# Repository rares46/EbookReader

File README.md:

# EbookReader
OpenBook eBook Reader

Dispozitivul e-book se bazeaza pe un microcontroller ESP32-C6 si include un afisaj E-Paper.

[Diagrama Bloc](Images/diagram.png)

`Diagrama bloc afiseaza componente:`
- ESP32-C6 (unitate centrala)
- Afisaj E-Paper
- Cititor SD card
- RTC DS3231
- Senzor ambiental BME688
- Control incarcare baterie Li-Po
- Modul flash extern 64MB
- Interfata USB-C
- Circuit de reglare tensiune (LDO)

### BOM - Bill Of Materials

[Fisier BOM](Manufacturing/BOM.csv)
https://ro.mouser.com/
https://www.comet.srl.ro/

Alimentare
- Alimentare principala prin USB-C.
- Reglator de tensiune LDO (IC4 - XC6204A33) pentru conversia de la 5V la 3.3V.
  
Microcontroller
- ESP32-C6 = unitatea principala ce controleaza restul pieselor.
- Se ocupa cu gestionarea interfetei cu utilizatorul, afisajul EPD, comunicatia cu SD card-ul, RTC si senzorul ambiental.
  
Stocare
- Slot microSD pentru stocare.
- Memorie flash externa W25Q512JVSIQ conectata prin SPI pentru firmware suplimentar sau caching.

### Alocarea pinilor ESP32-C6

| Functie                | Pin ESP32-C6         | Observatii |
|------------------------|----------------------|-------------|
| SD Card                | IO2, IO3, IO4, IO5   | SPI |
| E-Paper Display        | IO8, IO9, IO10       | SPI |
| Senzor BME688          | IO6 (SCL), IO7 (SDA) | I2C |
| RTC DS3231             | IO6 (SCL), IO7 (SDA) | I2C shared |
| Flash extern SPI       | IO0, IO1, IO2        | SPI |
| Boot Button            | IO9                  | Reset GPIO |
| Buton IO               | IO10                 | Control interfata |
| UART Debug             | IO20 (TX), IO21 (RX) | Conexiune seriala |
| Ecran Type Select      | IO18, IO19           | Selectare tip e-paper |

Bugs: La piesa SAMACSYS_PARTS_USB4110GFA erori cu Board OUtline Clearance, care sunt datorate piesei cel mai probabil si din cand in cand eorare de Overlap la fir. Daca scot firul si il pun la loc dispare.
La piesa IND_4828-WE-TPC_WRE 2 erori Copper Width, care probabil sunt de la piesa.
  
La directorul images din proiect sunt imagini cu schematic ul, pcb si 3d si diagrama.

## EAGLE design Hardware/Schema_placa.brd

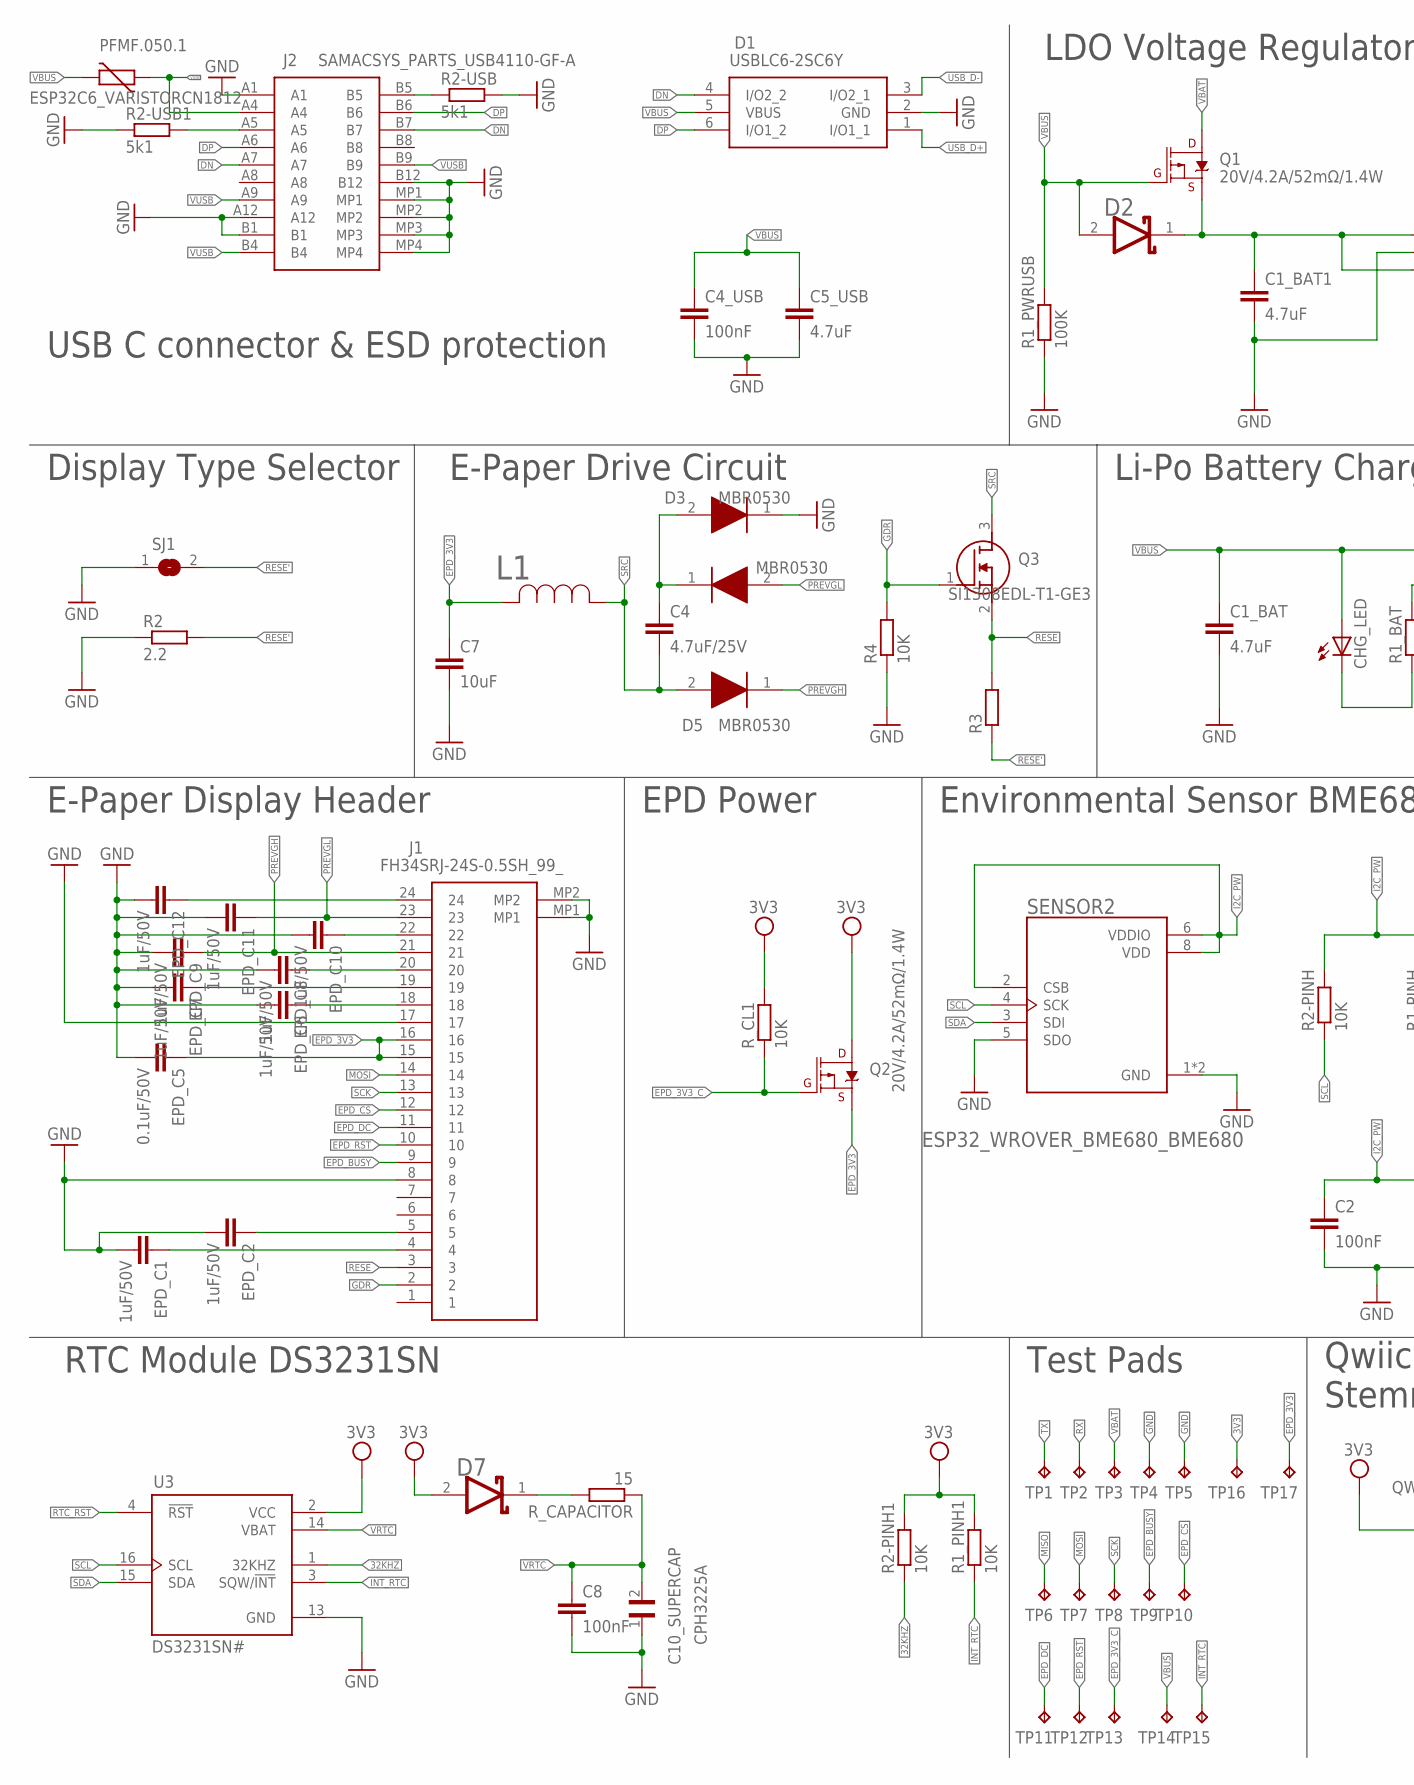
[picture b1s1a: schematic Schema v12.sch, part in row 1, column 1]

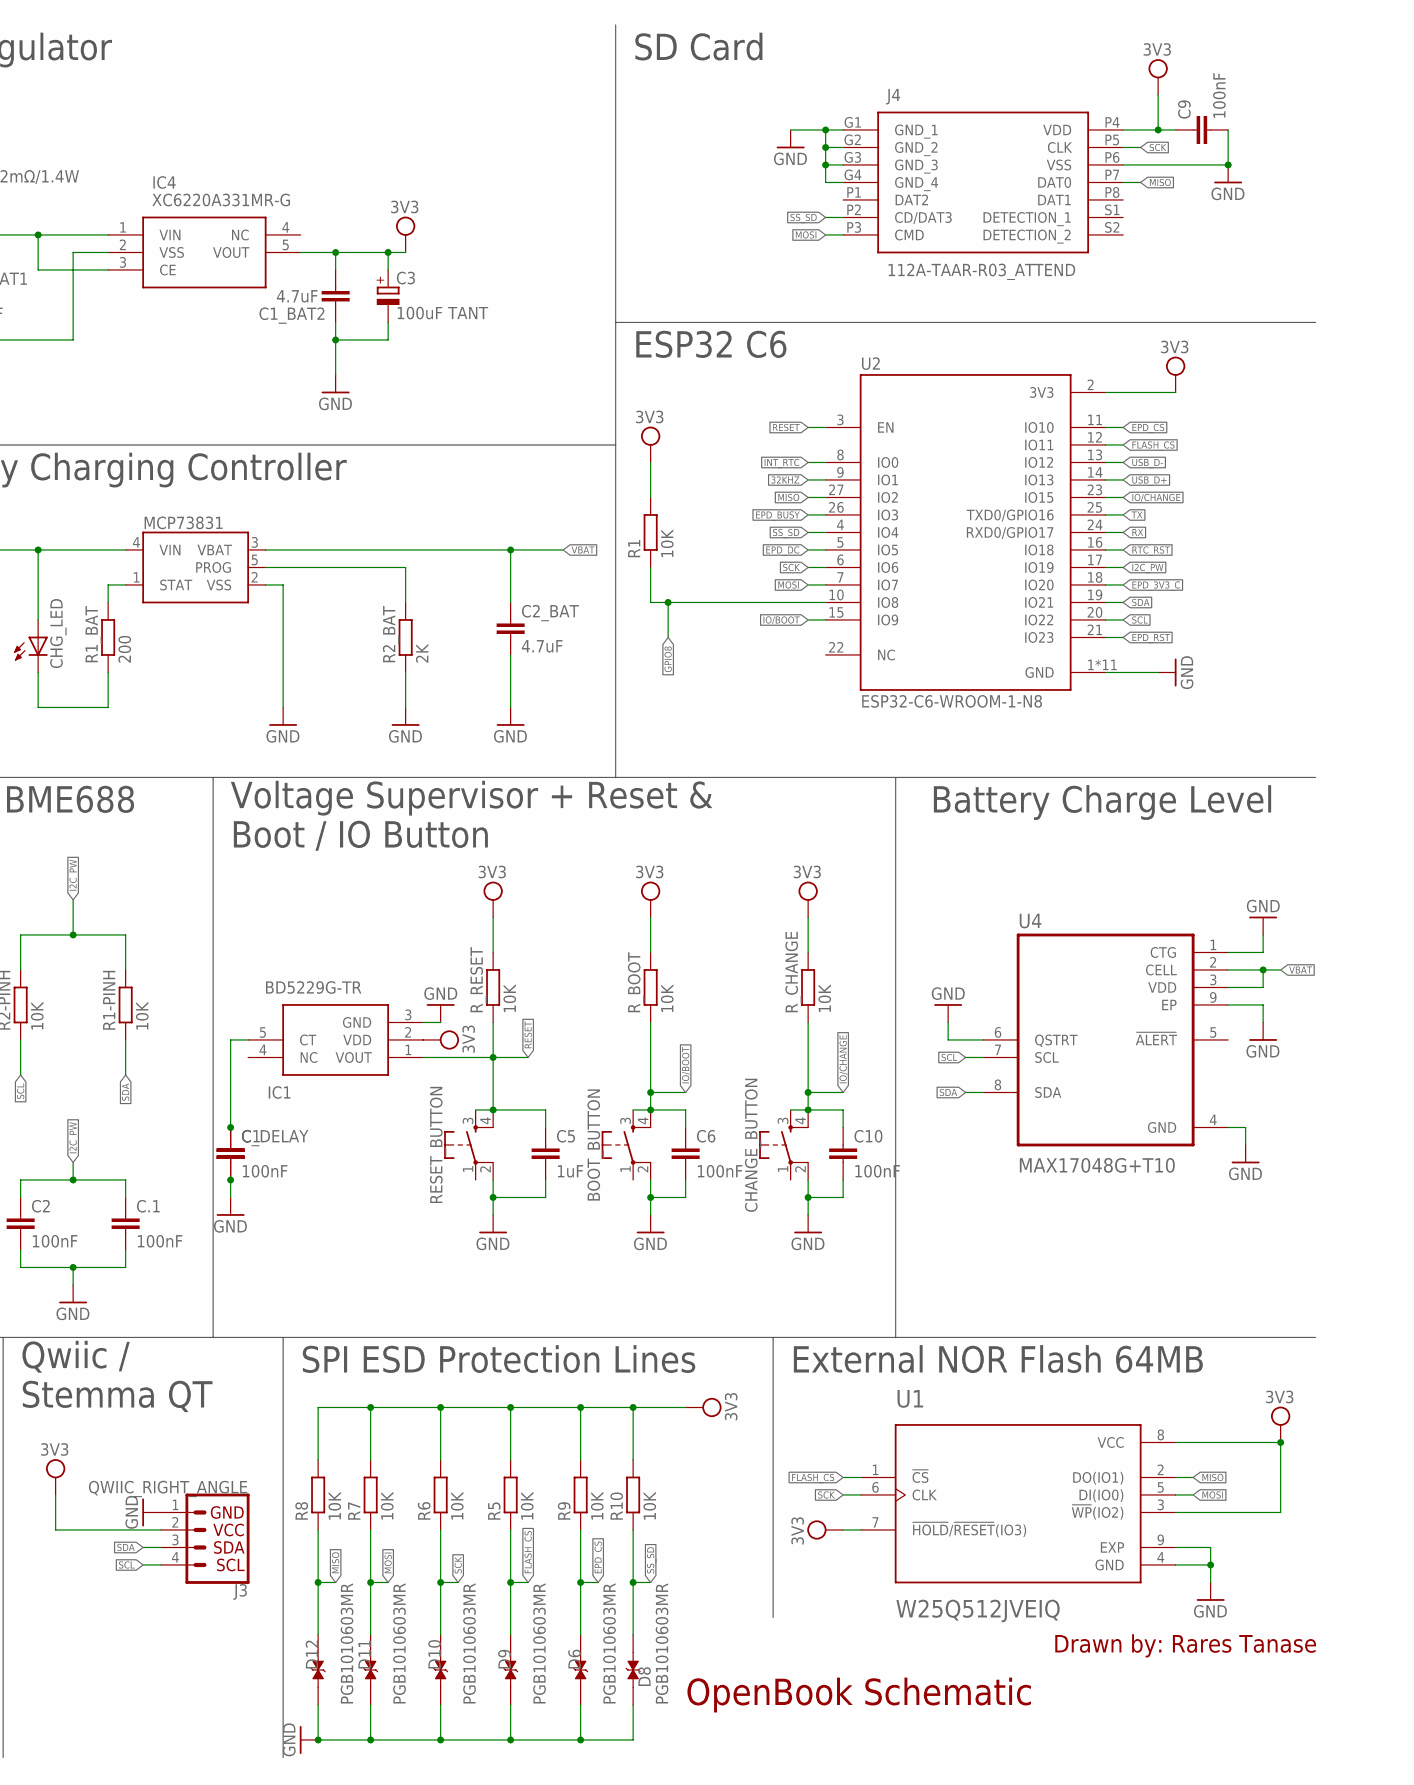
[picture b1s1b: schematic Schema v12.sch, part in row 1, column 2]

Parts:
BOOT_BUTTON: BUTTON_CUSYOMV1; MYBUTTON
C1: ESP32_WROVER_EAGLE-LTSPICE_CC0402; ESP32_WROVER_EAGLE-LTSPICE_C0402
C1_BAT, C1_BAT1, C1_BAT2, C2_BAT, C5_USB: 4.7uF; ESP32_WROVER_EAGLE-LTSPICE_C0402
C2, C4_USB, C6, C8, C9, C10, C.1: 100nF; ESP32_WROVER_EAGLE-LTSPICE_C0402
C3: 100uF TANT; RCL_CT3528
C4: 4.7uF/25V; ESP32_WROVER_EAGLE-LTSPICE_C0402
C5: 1uF; ESP32_WROVER_EAGLE-LTSPICE_C0402
C7: 10uF; ESP32_WROVER_EAGLE-LTSPICE_C0402
C10_SUPERCAP: CPH3225A; CAPCP3225X100N
CHANGE_BUTTON: BUTTON_CUSYOMV1; MYBUTTON
CHG_LED: ADAFRUIT_LEDCHIP-LED0603; ADAFRUIT_CHIP-LED0603
C_DELAY: 100nF; ESP32_WROVER_EAGLE-LTSPICE_C0402
D1: USBLC6-2SC6Y; SOT95P280X145-6N
D2, D7: ESP32_WROVER_AVX---SD0805S020S1R0_AVX_SD0805S020S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; ESP32_WROVER_AVX---SD0805S020S1R0_AVX_SD0805S020S1R0_0
D3, D4, D5: MBR0530; SOD3716X135N
D6, D8, D9, D10, D11, D12: PGB1010603MR; DIOC1608X36N
EPD_C1, EPD_C2, EPD_C6, EPD_C7, EPD_C8, EPD_C9, EPD_C10, EPD_C11, EPD_C12: 1uF/50V; ESP32_WROVER_EAGLE-LTSPICE_C0402
EPD_C5: 0.1uF/50V; ESP32_WROVER_EAGLE-LTSPICE_C0402
IC1: BD5229G-TR; SOT95P280X125-5N
IC4: XC6220A331MR-G; SOT95P280X120-5N
J1: FH34SRJ-24S-0.5SH_99_; FH34SRJ24S05SH99
J2: SAMACSYS_PARTS_USB4110-GF-A; SAMACSYS_PARTS_USB4110GFA
J3: QWIIC_RIGHT_ANGLE; JST04_1MM_RA
J4: 112A-TAAR-R03_ATTEND; 112ATAARR03ATTEND
L1: 744043680IND_4828-WE-TPC_WRE; IND_4828-WE-TPC_WRE
MCP73831: ESP32_WROVER_SPARKFUN-IC-POWER_MCP73831; ESP32_WROVER_SPARKFUN-IC-POWER_SOT23-5
PFMF.050.1: ESP32C6_VARISTORCN1812; ESP32C6_VARISTOR_CT/CN1812
Q1, Q2: 20V/4.2A/52mΩ/1.4W; ESP32_WROVER_SPARKFUN-DISCRETESEMI_SOT23-3
Q3: SI1308EDL-T1-GE3; SOT65P210X110-3N
R1, R1-PINH, R1_PINH1, R2-PINH, R2-PINH1, R4, R5, R6, R7, R8, R9, R10: 10K; ESP32_WROVER_EAGLE-LTSPICE_R0402
R1_BAT: 200; ESP32_WROVER_EAGLE-LTSPICE_R0402
R1_PWRUSB: 100K; ESP32_WROVER_EAGLE-LTSPICE_R0402
R2: 2.2; ESP32_WROVER_EAGLE-LTSPICE_R0402
R2-USB, R2-USB1: 5k1; ESP32_WROVER_EAGLE-LTSPICE_R0402
R2_BAT: 2K; ESP32_WROVER_EAGLE-LTSPICE_R0402
R3: ESP32_WROVER_EAGLE-LTSPICE_RR0402; ESP32_WROVER_EAGLE-LTSPICE_R0402
RESET_BUTTON: BUTTON_CUSYOMV1; MYBUTTON
R_BOOT: 10K; ESP32_WROVER_EAGLE-LTSPICE_R0402
R_CAPACITOR: 15; ESP32_WROVER_EAGLE-LTSPICE_R0402
R_CHANGE: 10K; ESP32_WROVER_EAGLE-LTSPICE_R0402
R_CL1: 10K; ESP32_WROVER_EAGLE-LTSPICE_R0402
R_RESET: 10K; ESP32_WROVER_EAGLE-LTSPICE_R0402
SENSOR2: ESP32_WROVER_BME680_BME680; ESP32_WROVER_BME680_PSON80P300X300X100-8N
SJ1: SJ
TP1, TP2, TP3, TP4, TP5, TP6, TP7, TP8, TP9, TP10, TP11, TP12, TP13, TP14, TP15, TP16, TP17: TPTP20R; TP20R
U1: W25Q512JVEIQ; SON127P600X800X80-9N
U2: ESP32-C6-WROOM-1-N8; XCVR_ESP32-C6-WROOM-1-N8
U3: DS3231SN#; SOIC127P1032X265-16N
U4: MAX17048G+T10; SON50P200X200X80-9N

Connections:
3V3: C1_BAT2.1, C3.+, C9.1, D7.2 (ANODE), IC1.2 (VDD), IC4.5 (VOUT), J3.2, J4.P4 (VDD), Q2.3 (D), R1.2, R1_PINH1.2, R2-PINH1.2, R5.2, R6.2, R7.2, R8.2, R9.2, R10.2, R_BOOT.2, R_CHANGE.2, R_CL1.2, R_RESET.2, TP16.TP, U1.3 (!WP!(IO2)), U1.7 (!HOLD!/!RESET!(IO3)), U1.8 (VCC), U2.2 (3V3), U3.2 (VCC)
32KHZ: R2-PINH1.1, U2.9 (IO1), U3.1 (32KHZ)
DN: D1.4 (I/O2_2), J2.A7, J2.B7
DP: D1.6 (I/O1_2), J2.A6, J2.B6
EPD_3V3: C7.1, EPD_C5.1, J1.15, J1.16, L1.2, Q2.2 (S), TP17.TP
EPD_3V3_C: Q2.1 (G), R_CL1.1, TP13.TP, U2.18 (IO20)
EPD_BUSY: J1.9, TP9.TP, U2.26 (IO3)
EPD_CS: D6.2, J1.12, R9.1, TP10.TP, U2.11 (IO10)
EPD_DC: J1.11, TP11.TP, U2.5 (IO5)
EPD_RST: J1.10, TP12.TP, U2.21 (IO23)
FLASH_CS: D9.2, R5.1, U1.1 (!CS), U2.12 (IO11)
GDR: J1.2, Q3.1 (G), R4.2
GND: BOOT_BUTTON.2, C1.2, C1_BAT.2, C1_BAT1.2, C1_BAT2.2, C2.2, C2_BAT.2, C3.-, C4_USB.2, C5.2, C5_USB.2, C6.2, C7.2, C8.2, C9.2, C10.2, C10_SUPERCAP.1, C.1.2, CHANGE_BUTTON.2, C_DELAY.2, D3.1 (K), D6.1, D8.1, D9.1, D10.1, D11.1, D12.1, EPD_C1.2, EPD_C2.2, EPD_C5.2, EPD_C6.2, EPD_C7.2, EPD_C8.2, EPD_C9.2, EPD_C10.2, EPD_C11.2, EPD_C12.2, IC1.3 (GND), IC4.2 (VSS), J1.8, J1.17, J1.MP1, J1.MP2, J2.A1, J2.A12, J2.B1, J2.B12, J2.MP1, J2.MP2, J2.MP3, J2.MP4, J3.1, J4.G1 (GND_1), J4.G2 (GND_2), J4.G3 (GND_3), J4.G4 (GND_4), J4.P6 (VSS), MCP73831.2 (VSS), R1_PWRUSB.1, R2.1, R2-USB.2, R2-USB1.1, R2_BAT.1, R4.1, RESET_BUTTON.2, SENSOR2.1 (GND), SENSOR2.5 (SDO), SENSOR2.7 (GND), SJ1.1, TP4.TP, TP5.TP, U1.4 (GND), U1.9 (EXP), U2.1 (GND), U2.28 (GND), U2.29_1 (GND), U2.29_2 (GND), U2.29_3 (GND), U2.29_4 (GND), U2.29_5 (GND), U2.29_6 (GND), U2.29_7 (GND), U2.29_8 (GND), U2.29_9 (GND), U3.13 (GND), U4.1 (CTG), U4.4 (GND), U4.6 (QSTRT), U4.9 (EP)
GPIO8: R1.1, U2.10 (IO8)
I2C_PW: C2.1, C.1.1, R1-PINH.2, R2-PINH.2, SENSOR2.2 (CSB), SENSOR2.6 (VDDIO), SENSOR2.8 (VDD), U2.17 (IO19)
INT_RTC: R1_PINH1.1, TP15.TP, U2.8 (IO0), U3.3 (SQW/!INT)
IO/BOOT: BOOT_BUTTON.3, BOOT_BUTTON.4, C6.1, R_BOOT.1, U2.15 (IO9)
IO/CHANGE: C10.1, CHANGE_BUTTON.3, CHANGE_BUTTON.4, R_CHANGE.1, U2.23 (IO15)
MISO: D12.2, J4.P7 (DAT0), R8.1, TP6.TP, U1.2 (DO(IO1)), U2.27 (IO2)
MOSI: D11.2, J1.14, J4.P3 (CMD), R7.1, TP7.TP, U1.5 (DI(IO0)), U2.7 (IO7)
unnamed: C1.1, C_DELAY.1, IC1.5 (CT)
unnamed: J2.B5, R2-USB.1
unnamed: EPD_C2.1, J1.5
unnamed: J2.A5, R2-USB1.2
unnamed: CHG_LED.C, R1_BAT.1
unnamed: C1_BAT1.1, D2.1 (CATHODE), IC4.1 (VIN), IC4.3 (CE), Q1.2 (S)
unnamed: C4.1, D3.2 (A), D4.1 (K)
unnamed: MCP73831.1 (STAT), R1_BAT.2
unnamed: MCP73831.5 (PROG), R2_BAT.2
unnamed: EPD_C1.1, J1.4
unnamed: EPD_C6.1, J1.18
unnamed: EPD_C7.1, J1.19
unnamed: EPD_C8.1, J1.20
unnamed: EPD_C10.1, J1.22
unnamed: EPD_C12.1, J1.24
unnamed: D7.1 (CATHODE), R_CAPACITOR.2
PREVGH: D5.1 (K), EPD_C9.1, J1.21
PREVGL: D4.2 (A), EPD_C11.1, J1.23
RESE: J1.3, Q3.2 (S), R3.2
RESE': R2.2, R3.1, SJ1.2
RESET: C5.1, IC1.1 (VOUT), RESET_BUTTON.3, RESET_BUTTON.4, R_RESET.1, U2.3 (EN)
RTC_RST: U2.16 (IO18), U3.4 (!RST)
RX: TP2.TP, U2.24 (RXD0/GPIO17)
SCK: D10.2, J1.13, J4.P5 (CLK), R6.1, TP8.TP, U1.6 (CLK), U2.6 (IO6)
SCL: J3.4, R2-PINH.1, SENSOR2.4 (SCK), U2.20 (IO22), U3.16 (SCL), U4.7 (SCL)
SDA: J3.3, R1-PINH.1, SENSOR2.3 (SDI), U2.19 (IO21), U3.15 (SDA), U4.8 (SDA)
SRC: C4.2, D5.2 (A), L1.1, Q3.3 (D)
SS_SD: D8.2, J4.P2 (CD/DAT3), R10.1, U2.4 (IO4)
TX: TP1.TP, U2.25 (TXD0/GPIO16)
USB_D+: D1.1 (I/O1_1), U2.14 (IO13)
USB_D-: D1.3 (I/O2_1), U2.13 (IO12)
VBAT: C2_BAT.1, MCP73831.3 (VBAT), Q1.3 (D), TP3.TP, U4.2 (CELL), U4.3 (VDD)
VBUS: C1_BAT.1, C4_USB.1, C5_USB.1, CHG_LED.A, D1.5 (VBUS), D2.2 (ANODE), MCP73831.4 (VIN), PFMF.050.1.2, Q1.1 (G), R1_PWRUSB.2, TP14.TP
VRTC: C8.1, C10_SUPERCAP.2, R_CAPACITOR.1, U3.14 (VBAT)
VUSB: J2.A4, J2.A9, J2.B4, J2.B9, PFMF.050.1.1

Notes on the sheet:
USB C connector & ESD protection
LDO Voltage Regulator
SD Card
Display Type Selector
E-Paper Drive Circuit
Li-Po Battery Charging Controller
ESP32 C6
E-Paper Display Header
EPD Power
Environmental Sensor BME688
Voltage Supervisor + Reset & Boot / IO Button
Battery Charge Level
RTC Module DS3231SN
Test Pads
Qwiic / Stemma QT
SPI ESD Protection Lines
External NOR Flash 64MB
OpenBook Schematic
Drawn by: Rares Tanase

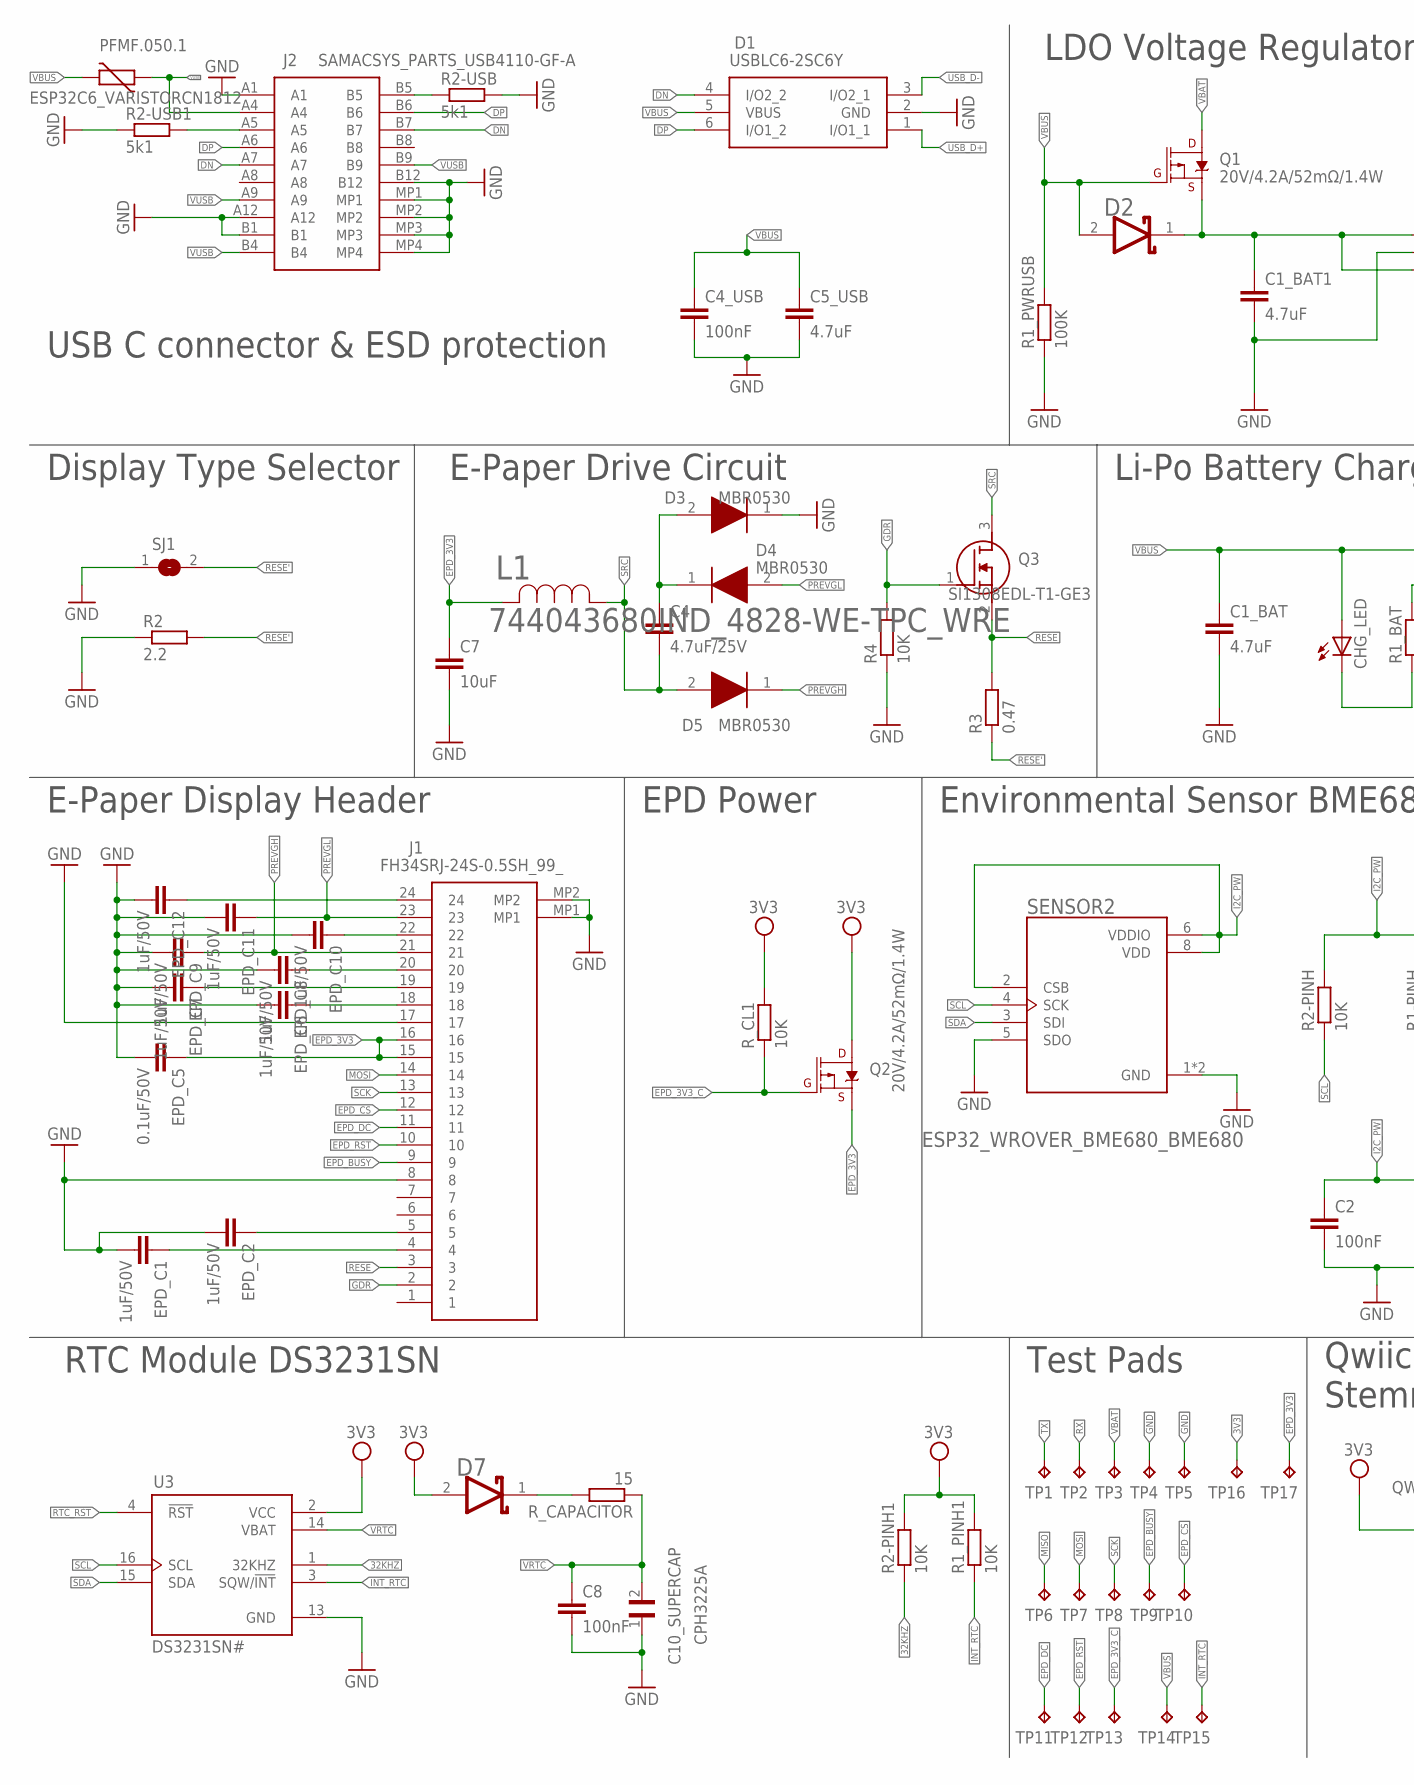
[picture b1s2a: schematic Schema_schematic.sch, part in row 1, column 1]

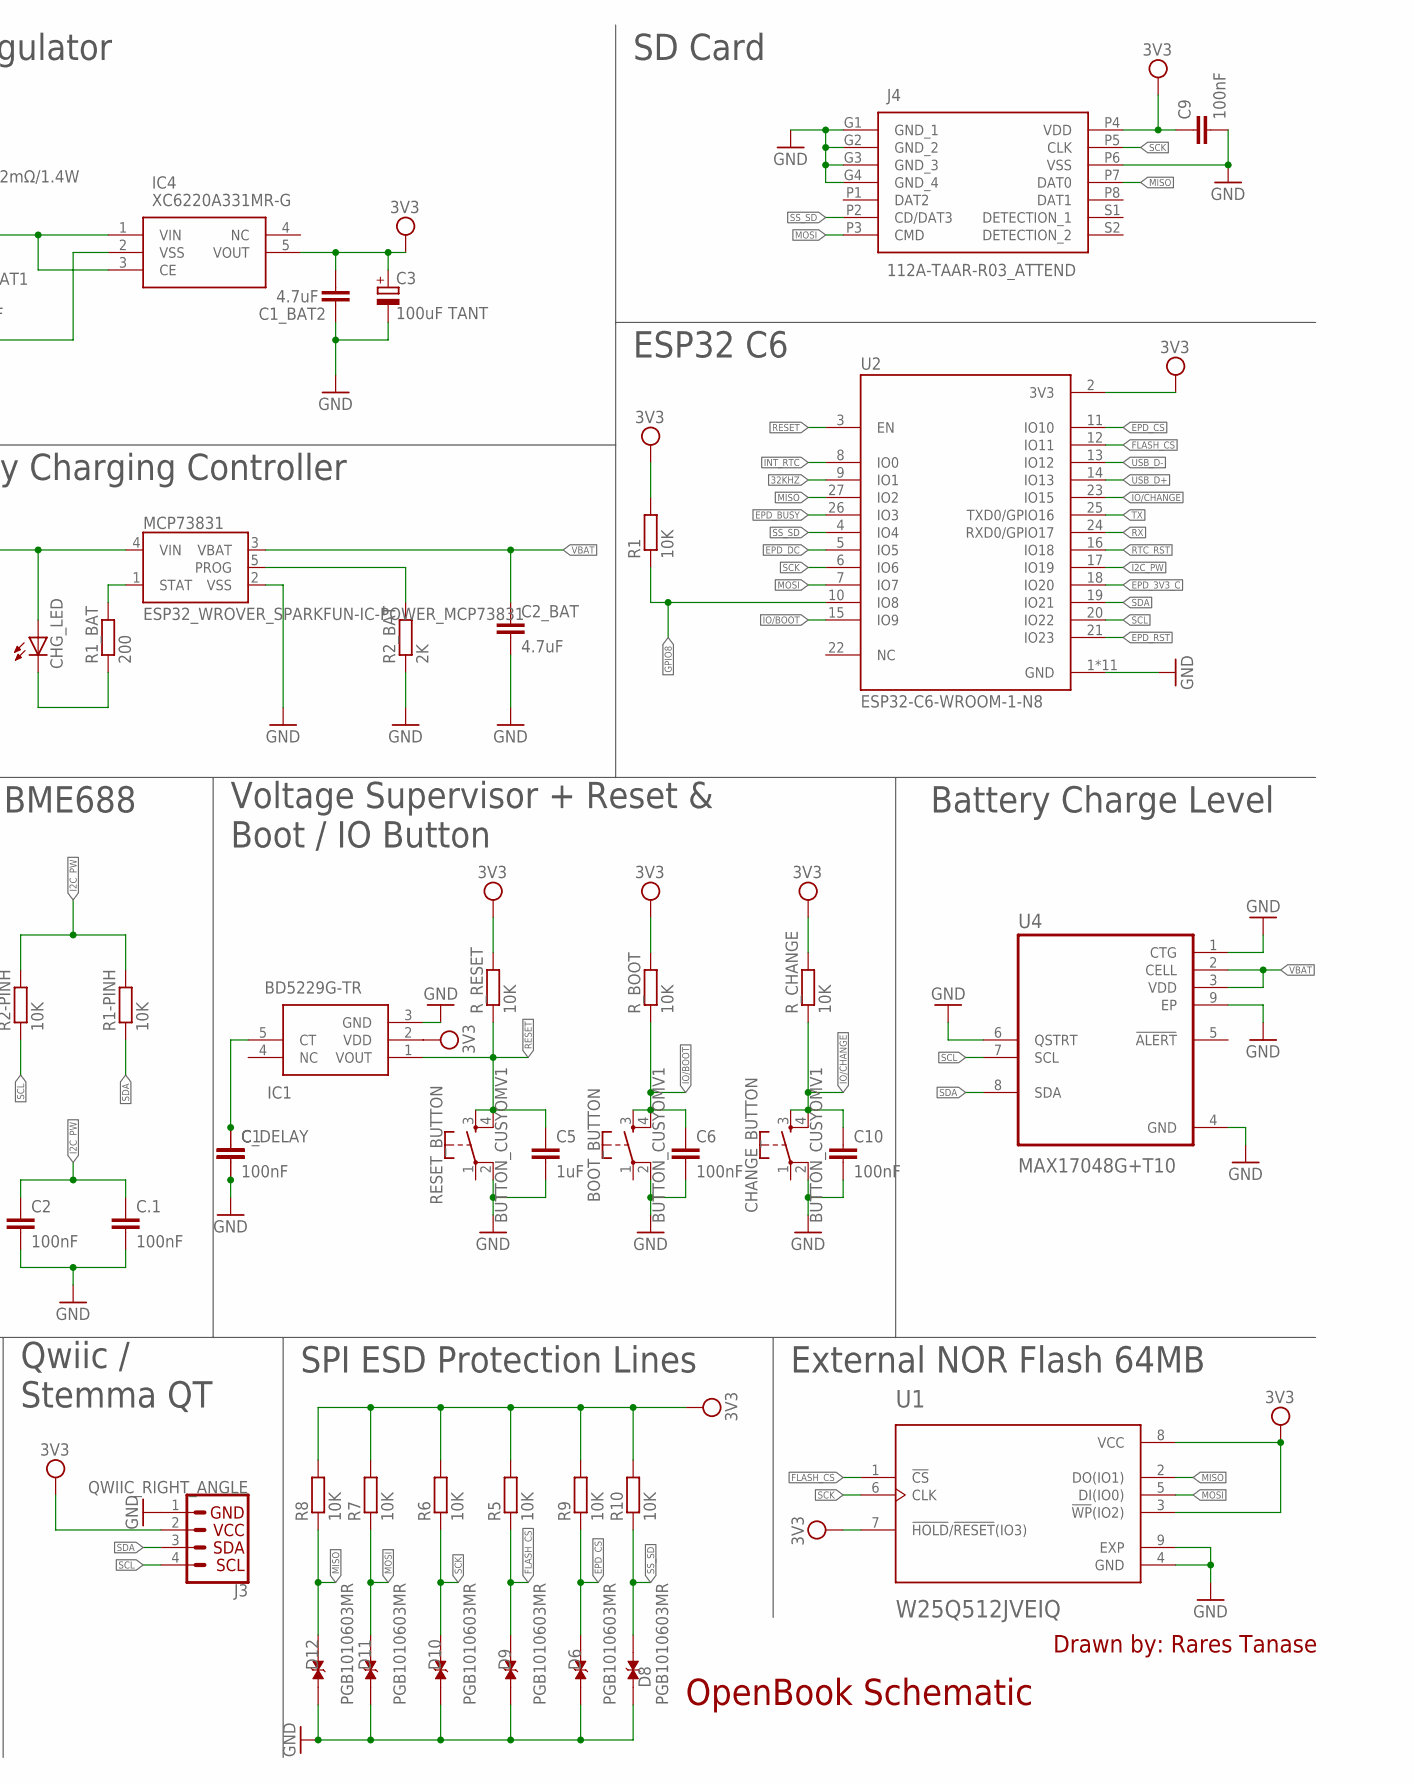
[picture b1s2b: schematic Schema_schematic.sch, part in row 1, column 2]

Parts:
BOOT_BUTTON: BUTTON_CUSYOMV1; MYBUTTON
C1: ESP32_WROVER_EAGLE-LTSPICE_CC0402; ESP32_WROVER_EAGLE-LTSPICE_C0402
C1_BAT, C1_BAT1, C1_BAT2, C2_BAT, C5_USB: 4.7uF; ESP32_WROVER_EAGLE-LTSPICE_C0402
C2, C4_USB, C6, C8, C9, C10, C.1: 100nF; ESP32_WROVER_EAGLE-LTSPICE_C0402
C3: 100uF TANT; RCL_CT3528
C4: 4.7uF/25V; ESP32_WROVER_EAGLE-LTSPICE_C0402
C5: 1uF; ESP32_WROVER_EAGLE-LTSPICE_C0402
C7: 10uF; ESP32_WROVER_EAGLE-LTSPICE_C0402
C10_SUPERCAP: CPH3225A; CAPCP3225X100N
CHANGE_BUTTON: BUTTON_CUSYOMV1; MYBUTTON
CHG_LED: ADAFRUIT_LEDCHIP-LED0603; ADAFRUIT_CHIP-LED0603
C_DELAY: 100nF; ESP32_WROVER_EAGLE-LTSPICE_C0402
D1: USBLC6-2SC6Y; SOT95P280X145-6N
D2, D7: ESP32_WROVER_AVX---SD0805S020S1R0_AVX_SD0805S020S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; ESP32_WROVER_AVX---SD0805S020S1R0_AVX_SD0805S020S1R0_0
D3, D4, D5: MBR0530; SOD3716X135N
D6, D8, D9, D10, D11, D12: PGB1010603MR; DIOC1608X36N
EPD_C1, EPD_C2, EPD_C6, EPD_C7, EPD_C8, EPD_C9, EPD_C10, EPD_C11, EPD_C12: 1uF/50V; ESP32_WROVER_EAGLE-LTSPICE_C0402
EPD_C5: 0.1uF/50V; ESP32_WROVER_EAGLE-LTSPICE_C0402
IC1: BD5229G-TR; SOT95P280X125-5N
IC4: XC6220A331MR-G; SOT95P280X120-5N
J1: FH34SRJ-24S-0.5SH_99_; FH34SRJ24S05SH99
J2: SAMACSYS_PARTS_USB4110-GF-A; SAMACSYS_PARTS_USB4110GFA
J3: QWIIC_RIGHT_ANGLE; JST04_1MM_RA
J4: 112A-TAAR-R03_ATTEND; 112ATAARR03ATTEND
L1: 744043680IND_4828-WE-TPC_WRE; IND_4828-WE-TPC_WRE
MCP73831: ESP32_WROVER_SPARKFUN-IC-POWER_MCP73831; ESP32_WROVER_SPARKFUN-IC-POWER_SOT23-5
PFMF.050.1: ESP32C6_VARISTORCN1812; ESP32C6_VARISTOR_CT/CN1812
Q1, Q2: 20V/4.2A/52mΩ/1.4W; ESP32_WROVER_SPARKFUN-DISCRETESEMI_SOT23-3
Q3: SI1308EDL-T1-GE3; SOT65P210X110-3N
R1, R1-PINH, R1_PINH1, R2-PINH, R2-PINH1, R4, R5, R6, R7, R8, R9, R10: 10K; ESP32_WROVER_EAGLE-LTSPICE_R0402
R1_BAT: 200; ESP32_WROVER_EAGLE-LTSPICE_R0402
R1_PWRUSB: 100K; ESP32_WROVER_EAGLE-LTSPICE_R0402
R2: 2.2; ESP32_WROVER_EAGLE-LTSPICE_R0402
R2-USB, R2-USB1: 5k1; ESP32_WROVER_EAGLE-LTSPICE_R0402
R2_BAT: 2K; ESP32_WROVER_EAGLE-LTSPICE_R0402
R3: 0.47; ESP32_WROVER_EAGLE-LTSPICE_R0402
RESET_BUTTON: BUTTON_CUSYOMV1; MYBUTTON
R_BOOT: 10K; ESP32_WROVER_EAGLE-LTSPICE_R0402
R_CAPACITOR: 15; ESP32_WROVER_EAGLE-LTSPICE_R0402
R_CHANGE: 10K; ESP32_WROVER_EAGLE-LTSPICE_R0402
R_CL1: 10K; ESP32_WROVER_EAGLE-LTSPICE_R0402
R_RESET: 10K; ESP32_WROVER_EAGLE-LTSPICE_R0402
SENSOR2: ESP32_WROVER_BME680_BME680; ESP32_WROVER_BME680_PSON80P300X300X100-8N
SJ1: SJ
TP1, TP2, TP3, TP4, TP5, TP6, TP7, TP8, TP9, TP10, TP11, TP12, TP13, TP14, TP15, TP16, TP17: TPTP20R; TP20R
U1: W25Q512JVEIQ; SON127P600X800X80-9N
U2: ESP32-C6-WROOM-1-N8; XCVR_ESP32-C6-WROOM-1-N8
U3: DS3231SN#; SOIC127P1032X265-16N
U4: MAX17048G+T10; SON50P200X200X80-9N

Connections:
3V3: C1_BAT2.1, C3.+, C9.1, D7.2 (ANODE), IC1.2 (VDD), IC4.5 (VOUT), J3.2, J4.P4 (VDD), Q2.3 (D), R1.2, R1_PINH1.2, R2-PINH1.2, R5.2, R6.2, R7.2, R8.2, R9.2, R10.2, R_BOOT.2, R_CHANGE.2, R_CL1.2, R_RESET.2, TP16.TP, U1.3 (!WP!(IO2)), U1.7 (!HOLD!/!RESET!(IO3)), U1.8 (VCC), U2.2 (3V3), U3.2 (VCC)
32KHZ: R2-PINH1.1, U2.9 (IO1), U3.1 (32KHZ)
DN: D1.4 (I/O2_2), J2.A7, J2.B7
DP: D1.6 (I/O1_2), J2.A6, J2.B6
EPD_3V3: C7.1, EPD_C5.1, J1.15, J1.16, L1.2, Q2.2 (S), TP17.TP
EPD_3V3_C: Q2.1 (G), R_CL1.1, TP13.TP, U2.18 (IO20)
EPD_BUSY: J1.9, TP9.TP, U2.26 (IO3)
EPD_CS: D6.2, J1.12, R9.1, TP10.TP, U2.11 (IO10)
EPD_DC: J1.11, TP11.TP, U2.5 (IO5)
EPD_RST: J1.10, TP12.TP, U2.21 (IO23)
FLASH_CS: D9.2, R5.1, U1.1 (!CS), U2.12 (IO11)
GDR: J1.2, Q3.1 (G), R4.2
GND: BOOT_BUTTON.2, C1.2, C1_BAT.2, C1_BAT1.2, C1_BAT2.2, C2.2, C2_BAT.2, C3.-, C4_USB.2, C5.2, C5_USB.2, C6.2, C7.2, C8.2, C9.2, C10.2, C10_SUPERCAP.1, C.1.2, CHANGE_BUTTON.2, C_DELAY.2, D3.1 (K), D6.1, D8.1, D9.1, D10.1, D11.1, D12.1, EPD_C1.2, EPD_C2.2, EPD_C5.2, EPD_C6.2, EPD_C7.2, EPD_C8.2, EPD_C9.2, EPD_C10.2, EPD_C11.2, EPD_C12.2, IC1.3 (GND), IC4.2 (VSS), J1.8, J1.17, J1.MP1, J1.MP2, J2.A1, J2.A12, J2.B1, J2.B12, J2.MP1, J2.MP2, J2.MP3, J2.MP4, J3.1, J4.G1 (GND_1), J4.G2 (GND_2), J4.G3 (GND_3), J4.G4 (GND_4), J4.P6 (VSS), MCP73831.2 (VSS), R1_PWRUSB.1, R2.1, R2-USB.2, R2-USB1.1, R2_BAT.1, R4.1, RESET_BUTTON.2, SENSOR2.1 (GND), SENSOR2.5 (SDO), SENSOR2.7 (GND), SJ1.1, TP4.TP, TP5.TP, U1.4 (GND), U1.9 (EXP), U2.1 (GND), U2.28 (GND), U2.29_1 (GND), U2.29_2 (GND), U2.29_3 (GND), U2.29_4 (GND), U2.29_5 (GND), U2.29_6 (GND), U2.29_7 (GND), U2.29_8 (GND), U2.29_9 (GND), U3.13 (GND), U4.1 (CTG), U4.4 (GND), U4.6 (QSTRT), U4.9 (EP)
GPIO8: R1.1, U2.10 (IO8)
I2C_PW: C2.1, C.1.1, R1-PINH.2, R2-PINH.2, SENSOR2.2 (CSB), SENSOR2.6 (VDDIO), SENSOR2.8 (VDD), U2.17 (IO19)
INT_RTC: R1_PINH1.1, TP15.TP, U2.8 (IO0), U3.3 (SQW/!INT)
IO/BOOT: BOOT_BUTTON.3, BOOT_BUTTON.4, C6.1, R_BOOT.1, U2.15 (IO9)
IO/CHANGE: C10.1, CHANGE_BUTTON.3, CHANGE_BUTTON.4, R_CHANGE.1, U2.23 (IO15)
MISO: D12.2, J4.P7 (DAT0), R8.1, TP6.TP, U1.2 (DO(IO1)), U2.27 (IO2)
MOSI: D11.2, J1.14, J4.P3 (CMD), R7.1, TP7.TP, U1.5 (DI(IO0)), U2.7 (IO7)
unnamed: C1.1, C_DELAY.1, IC1.5 (CT)
unnamed: J2.B5, R2-USB.1
unnamed: EPD_C2.1, J1.5
unnamed: J2.A5, R2-USB1.2
unnamed: CHG_LED.C, R1_BAT.1
unnamed: C1_BAT1.1, D2.1 (CATHODE), IC4.1 (VIN), IC4.3 (CE), Q1.2 (S)
unnamed: C4.1, D3.2 (A), D4.1 (K)
unnamed: MCP73831.1 (STAT), R1_BAT.2
unnamed: MCP73831.5 (PROG), R2_BAT.2
unnamed: EPD_C1.1, J1.4
unnamed: EPD_C6.1, J1.18
unnamed: EPD_C7.1, J1.19
unnamed: EPD_C8.1, J1.20
unnamed: EPD_C10.1, J1.22
unnamed: EPD_C12.1, J1.24
unnamed: D7.1 (CATHODE), R_CAPACITOR.2
PREVGH: D5.1 (K), EPD_C9.1, J1.21
PREVGL: D4.2 (A), EPD_C11.1, J1.23
RESE: J1.3, Q3.2 (S), R3.2
RESE': R2.2, R3.1, SJ1.2
RESET: C5.1, IC1.1 (VOUT), RESET_BUTTON.3, RESET_BUTTON.4, R_RESET.1, U2.3 (EN)
RTC_RST: U2.16 (IO18), U3.4 (!RST)
RX: TP2.TP, U2.24 (RXD0/GPIO17)
SCK: D10.2, J1.13, J4.P5 (CLK), R6.1, TP8.TP, U1.6 (CLK), U2.6 (IO6)
SCL: J3.4, R2-PINH.1, SENSOR2.4 (SCK), U2.20 (IO22), U3.16 (SCL), U4.7 (SCL)
SDA: J3.3, R1-PINH.1, SENSOR2.3 (SDI), U2.19 (IO21), U3.15 (SDA), U4.8 (SDA)
SRC: C4.2, D5.2 (A), L1.1, Q3.3 (D)
SS_SD: D8.2, J4.P2 (CD/DAT3), R10.1, U2.4 (IO4)
TX: TP1.TP, U2.25 (TXD0/GPIO16)
USB_D+: D1.1 (I/O1_1), U2.14 (IO13)
USB_D-: D1.3 (I/O2_1), U2.13 (IO12)
VBAT: C2_BAT.1, MCP73831.3 (VBAT), Q1.3 (D), TP3.TP, U4.2 (CELL), U4.3 (VDD)
VBUS: C1_BAT.1, C4_USB.1, C5_USB.1, CHG_LED.A, D1.5 (VBUS), D2.2 (ANODE), MCP73831.4 (VIN), PFMF.050.1.2, Q1.1 (G), R1_PWRUSB.2, TP14.TP
VRTC: C8.1, C10_SUPERCAP.2, R_CAPACITOR.1, U3.14 (VBAT)
VUSB: J2.A4, J2.A9, J2.B4, J2.B9, PFMF.050.1.1

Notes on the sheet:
USB C connector & ESD protection
LDO Voltage Regulator
SD Card
Display Type Selector
E-Paper Drive Circuit
Li-Po Battery Charging Controller
ESP32 C6
E-Paper Display Header
EPD Power
Environmental Sensor BME688
Voltage Supervisor + Reset & Boot / IO Button
Battery Charge Level
RTC Module DS3231SN
Test Pads
Qwiic / Stemma QT
SPI ESD Protection Lines
External NOR Flash 64MB
OpenBook Schematic
Drawn by: Rares Tanase

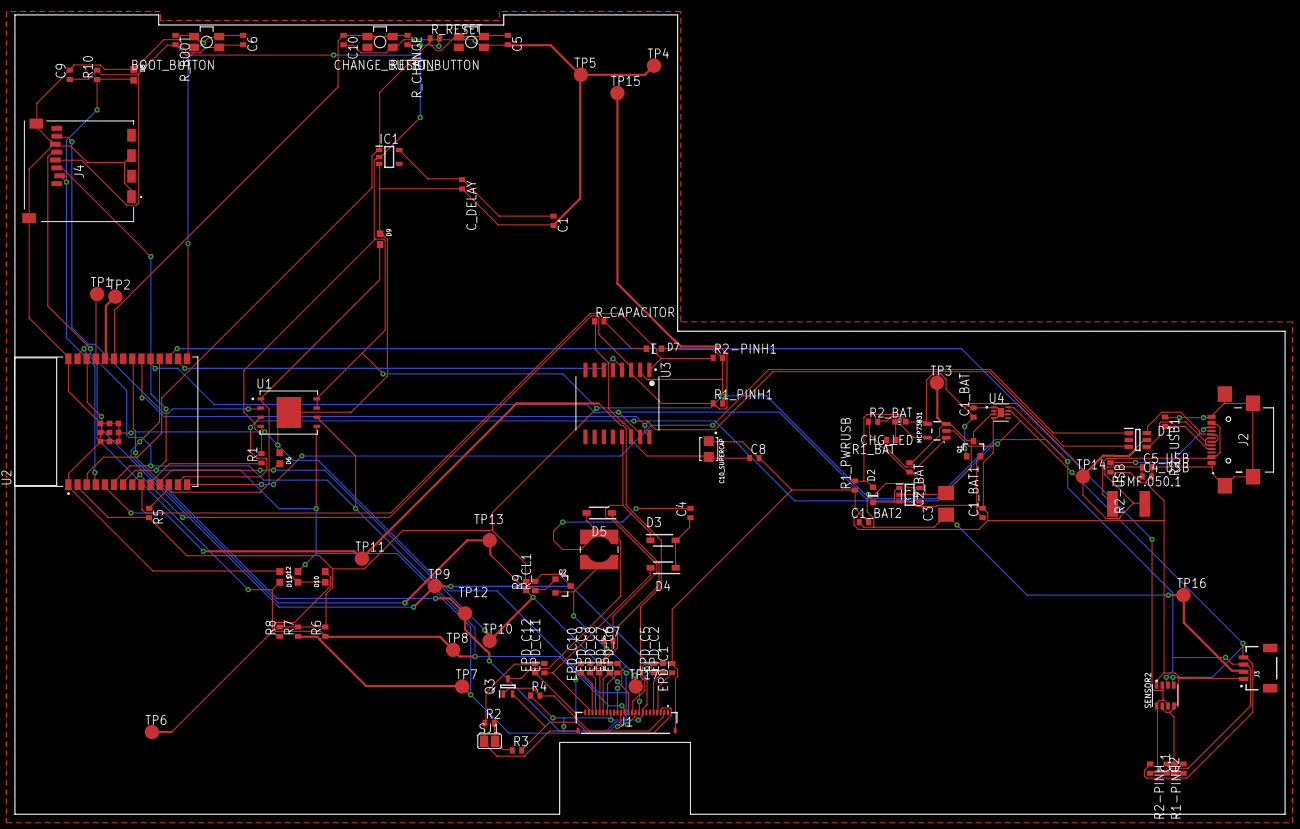
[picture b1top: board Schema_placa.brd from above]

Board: 2 copper layers, 176.7 x 111.2 mm, 104 parts (0 on the bottom side), 55 nets.

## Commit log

2025-04-07 Create LICENSE
2025-04-07 Update LICENSE

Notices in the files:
parts and their libraries:
DeskAssistant v19 v1: COPYRIGHT: Copyright (C) 2024 Ultra Librarian. All rights reserved.
